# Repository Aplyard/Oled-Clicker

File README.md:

# Oled Clicker

A simple counter, implementing an Arduino Nano, a lipo battery & an Oled Display 128x32.  
Made for no absolute reason  
Off course it can be hand-wired, but the enclosoure doesn't have enough space for wire spaghetti  

---

**Components**  
-
- [Arduino Nano](https://store.arduino.cc/arduino-nano#:~:text=The%20Arduino%20Nano%20is%20a,instead%20of%20a%20standard%20one.)    
- [tp4056 USB Lipo Charging Module](https://i.imgur.com/EEmYTeY.png)  
- 10k Resistor  
- [450mah 1cell Lipo (20h aprox. runtime)](https://i.imgur.com/DlrVCJd.png)  
- [0.91' Oled Display 128x32p](https://i.imgur.com/tNMHrN5.jpg)  
- Cherry MX Switch  
- 1 keycap :P

**3d Files**
-
You can all the 3d files needed here:
- [my Thingiverse repo](https://www.thingiverse.com/aplyard/designs)

**Designed**
-  
- [Fusion360](https://www.autodesk.com/products/fusion-360/overview)    
- [KiCad](https://github.com/KiCad)    
- [Arduino IDE](https://www.arduino.cc/en/main/software)

---   
Maintainer: Aplyard  
Hardware Supported: Nano ATmega328p  
Hardware Availability: Aplyard

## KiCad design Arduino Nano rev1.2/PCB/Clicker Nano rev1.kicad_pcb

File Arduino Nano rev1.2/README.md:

# Oled Clicker rev1.2
  
This  is an updated pcb of the Arduino Nano rev1.  
Disclaimer : Please double check pcb wiring and schematics. I am not responsible for any faults or technical issues. You can always feel free to adress any issue to me and i will try to work them out.

## Pcb Breakout

**Components**  
-
- Arduino Nano  
- [tp4056 USB Lipo Charging Module](https://i.imgur.com/EEmYTeY.png)  
- 10k Resistor  
- [450mah 1cell Lipo (20h aprox. runtime)](https://i.imgur.com/DlrVCJd.png)  
- [0.91' Oled Display 128x32p](https://i.imgur.com/tNMHrN5.jpg)  
- Cherry MX Switch  
- 1 keycap :P

**3d Files**
-
You can 3d files needed here:
- [my Thingiverse repo](https://www.thingiverse.com/aplyard/designs)

**Design**
- [KiCad](https://github.com/KiCad)    
- [Arduino IDE](https://www.arduino.cc/en/main/software)

---   
Maintainer: Aplyard  
Hardware Supported: Nano ATmega328p  
Hardware Availability: Aplyard

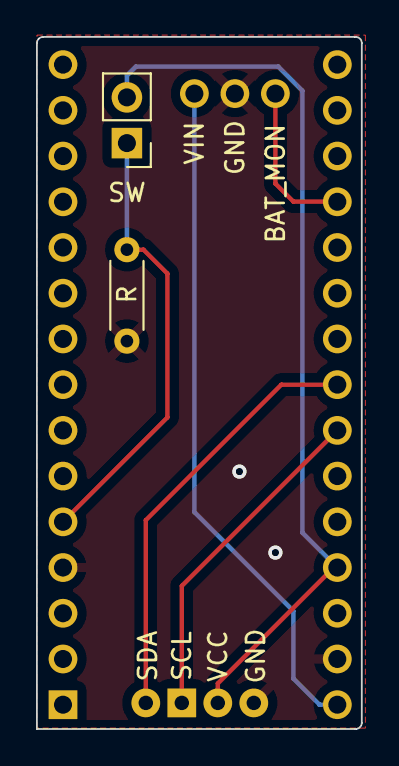
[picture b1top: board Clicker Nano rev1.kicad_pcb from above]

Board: 2 copper layers, 18.1 x 38.5 mm, 7 parts (1 on the bottom side), 7 nets.

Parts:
A1: Arduino_Nano_v2.x; Arduino_Nano
BAT_MON: SolderWirePad_1x01_SMD_1x2mm
GND: SolderWirePad_1x01_SMD_1x2mm
J1: Conn_01x04_Female; Oled 128x32
R: 10k; R_Axial_DIN0204_L3.6mm_D1.6mm_P5.08mm_Horizontal
SW: SW_Push; PinHeader_1x02_P2.54mm_Vertical
VIN: SolderWirePad_1x01_SMD_1x2mm

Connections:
+5V: A1.27 (+5V), J1.3, SW.2
/BAT_MON: A1.19 (A0), BAT_MON.1
/SCL: A1.24 (A5), J1.2
/SDA: A1.23 (A4), J1.1
/SWITCH: A1.5 (D2), R.2, SW.1
GND: A1.4 (GND), A1.29 (GND), GND.1, J1.4, R.1
VBUS: A1.30 (VIN), VIN.1

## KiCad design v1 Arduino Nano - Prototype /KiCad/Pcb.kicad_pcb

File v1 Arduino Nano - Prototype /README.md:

# Oled Clicker
https://github.com/Aplyard/Oled-Clicker

This is the v1 of the project.  
Handwired and tested.  

Pcb Breakout
-  

**Components**  
-
Arduino Nano  
[tp4056 USB Lipo Charging Module](https://i.imgur.com/EEmYTeY.png)  
10k Resistor  
[450mah 1cell Lipo (20h aprox. runtime)](https://i.imgur.com/DlrVCJd.png)  
[0.91' Oled Display 128x32p](https://i.imgur.com/tNMHrN5.jpg)  
Cherry MX Switch  
1 keycap :P

**3d Files**
-
You can all the 3d files needed here:
- [my Thingiverse repo](https://www.thingiverse.com/aplyard/designs)

**Design**
-  
    
[KiCad](https://github.com/KiCad)    
[Arduino IDE](https://www.arduino.cc/en/main/software)

---   
Maintainer: Aplyard  
Hardware Supported: Nano ATmega328p  
Hardware Availability: Aplyard

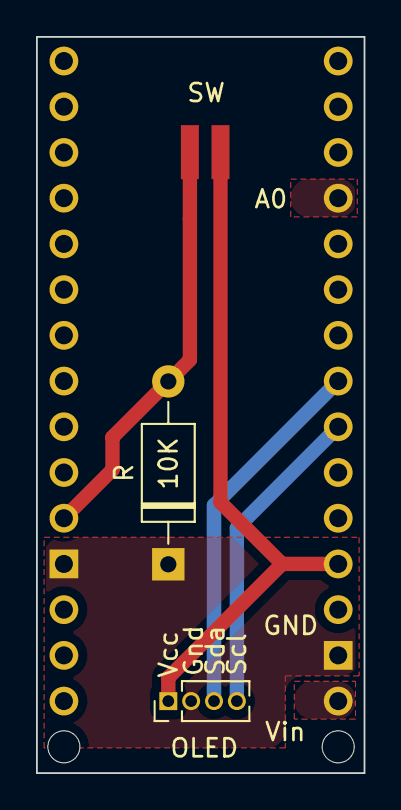
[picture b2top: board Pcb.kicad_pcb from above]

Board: 2 copper layers, 18.2 x 40.9 mm, 4 parts (1 on the bottom side), 5 nets.

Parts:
A1: Arduino_Nano; Arduino_Nano_WithMountingHoles
OLED: OLED; PinHeader_1x04_P1.27mm_Vertical
R: 10k; D_A-405_P10.16mm_Horizontal
SW: SW_PUSH; PinHeader_1x02_P1.27mm_Vertical_SMD_Pin1Right

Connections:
/A4: A1.23 (AD4/D18), OLED.3 (VCC)
/A5: A1.24 (AD5/D19), OLED.4 (GND)
/ARD5V: A1.27 (5V), OLED.1 (SDA), SW.1
GND: A1.4 (GND), A1.29 (GND), OLED.2 (SCL), R.1
unnamed: A1.5 (D2), R.2, SW.2

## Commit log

2020-09-25 photo
2020-09-25 in develop
2020-09-25 ignore
2020-09-25 Clean it out a bit
2020-09-25 clean
2020-09-25 new screenshots
2020-09-25 Update LICENSE
2020-09-26 3d files transfered to thingiverse
2020-11-19 rev1.2
2020-11-19 Photos
2020-11-19 names
2020-11-20 Arduino and Gerbers
